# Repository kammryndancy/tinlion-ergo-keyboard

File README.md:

# tinlion-ergo-keyboard

Keyboard layout and PCB customized for my hands specifically.

Generated using https://ergogen.cache.works/

PCB edited on KiCAD - PCBEditor

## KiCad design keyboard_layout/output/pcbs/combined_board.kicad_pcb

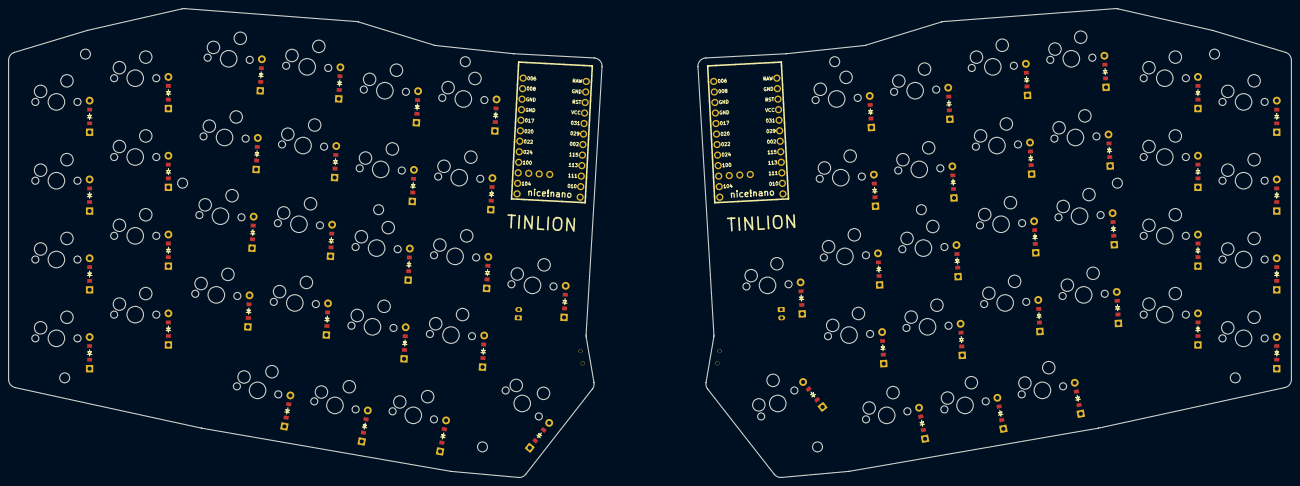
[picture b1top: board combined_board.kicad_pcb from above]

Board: 2 copper layers, 309.3 x 113.0 mm, 122 parts (0 on the bottom side), 84 nets, no tracks yet.

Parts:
D1, D2, D3, D4, D5, D6, D7, D8, D9, D10, D11, D12, D13, D14, D15, D16, D17, D18, D19, D20, D21, D22, D23, D24, D25, D26, D27, D28, D29, D30, D31, D32, D33, D34, D35, D36, D37, D38, D39, D40, D41, D42, D43, D44, D45, D46, D47, D48, D49, D50, D51, D52, D53, D54, D55, D56, D57, D58: ComboDiode
JST1, JST2: JST_PH_S2B-PH-K_02x2.00mm_Angled
MCU1, MCU2: nice_nano
S1, S2, S3, S4, S5, S6, S7, S8, S9, S10, S11, S12, S13, S14, S15, S16, S17, S18, S19, S20, S21, S22, S23, S24, S25, S26, S27, S28, S29, S30, S31, S32, S33, S34, S35, S36, S37, S38, S39, S40, S41, S42, S43, S44, S45, S46, S47, S48, S49, S50, S51, S52, S53, S54, S55, S56, S57, S58: MX
T1, T2: SPDT_C128955

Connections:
GND: JST1.2, JST2.2, MCU1.3, MCU1.4, MCU1.23, MCU2.3, MCU2.4, MCU2.23
P002: D2.1, D6.1, D10.1, D14.1, D18.1, D22.1, D29.1, D31.1, D35.1, D39.1, D43.1, D47.1, D51.1, D58.1, MCU1.18, MCU2.18
P006: MCU1.1, MCU2.1
P008: MCU1.2, MCU2.2
P009: MCU1.13, MCU2.13
P010: MCU1.14, MCU2.14
P011: MCU1.10, MCU2.10, S17.1, S18.1, S19.1, S20.1, S26.1, S46.1, S47.1, S48.1, S49.1, S55.1
P017: MCU1.5, MCU2.5, S28.1, S29.1, S57.1, S58.1
P020: MCU1.6, MCU2.6, S1.1, S2.1, S3.1, S4.1, S30.1, S31.1, S32.1, S33.1
P022: MCU1.7, MCU2.7, S5.1, S6.1, S7.1, S8.1, S34.1, S35.1, S36.1, S37.1
P024: MCU1.8, MCU2.8, S9.1, S10.1, S11.1, S12.1, S38.1, S39.1, S40.1, S41.1
P029: D3.1, D7.1, D11.1, D15.1, D19.1, D23.1, D32.1, D36.1, D40.1, D44.1, D48.1, D52.1, MCU1.19, MCU2.19
P031: D4.1, D8.1, D12.1, D16.1, D20.1, D24.1, D33.1, D37.1, D41.1, D45.1, D49.1, D53.1, MCU1.20, MCU2.20
P100: MCU1.9, MCU2.9, S13.1, S14.1, S15.1, S16.1, S25.1, S42.1, S43.1, S44.1, S45.1, S54.1
P101: MCU1.31, MCU2.31
P102: MCU1.32, MCU2.32
P104: MCU1.11, MCU2.11, S21.1, S22.1, S23.1, S24.1, S27.1, S50.1, S51.1, S52.1, S53.1, S56.1
P106: MCU1.12, MCU2.12
P107: MCU1.33, MCU2.33
P111: MCU1.15, MCU2.15
P113: D25.1, D26.1, D27.1, D28.1, D54.1, D55.1, D56.1, D57.1, MCU1.16, MCU2.16
P115: D1.1, D5.1, D9.1, D13.1, D17.1, D21.1, D30.1, D34.1, D38.1, D42.1, D46.1, D50.1, MCU1.17, MCU2.17
RAW: MCU1.24, MCU2.24, T1.2, T2.2
RST: MCU1.22, MCU2.22
VCC: MCU1.21, MCU2.21
curly_square: D29.2, S29.2
far_thumb: D27.2, S27.2
five_bottom: D21.2, S21.2
five_home: D22.2, S22.2
five_number: D24.2, S24.2
five_qwerty: D23.2, S23.2
four_bottom: D17.2, S17.2
four_home: D18.2, S18.2
four_number: D20.2, S20.2
four_qwerty: D19.2, S19.2
function_keys_bottom: D1.2, S1.2
function_keys_home: D2.2, S2.2
function_keys_number: D4.2, S4.2
function_keys_qwerty: D3.2, S3.2
home_thumb: D26.2, S26.2
mirror_curly_square: D58.2, S58.2
mirror_far_thumb: D56.2, S56.2
mirror_five_bottom: D50.2, S50.2
mirror_five_home: D51.2, S51.2
mirror_five_number: D53.2, S53.2
mirror_five_qwerty: D52.2, S52.2
mirror_four_bottom: D46.2, S46.2
mirror_four_home: D47.2, S47.2
mirror_four_number: D49.2, S49.2
mirror_four_qwerty: D48.2, S48.2
mirror_function_keys_bottom: D30.2, S30.2
mirror_function_keys_home: D31.2, S31.2
mirror_function_keys_number: D33.2, S33.2
mirror_function_keys_qwerty: D32.2, S32.2
mirror_home_thumb: D55.2, S55.2
mirror_near_thumb: D54.2, S54.2
mirror_one_bottom: D34.2, S34.2
mirror_one_home: D35.2, S35.2
mirror_one_number: D37.2, S37.2
mirror_one_qwerty: D36.2, S36.2
mirror_space_thumb: D57.2, S57.2
mirror_three_bottom: D42.2, S42.2
mirror_three_home: D43.2, S43.2
mirror_three_number: D45.2, S45.2
mirror_three_qwerty: D44.2, S44.2
mirror_two_bottom: D38.2, S38.2
mirror_two_home: D39.2, S39.2
mirror_two_number: D41.2, S41.2
mirror_two_qwerty: D40.2, S40.2
near_thumb: D25.2, S25.2
one_bottom: D5.2, S5.2
one_home: D6.2, S6.2
one_number: D8.2, S8.2
one_qwerty: D7.2, S7.2
pos: JST1.1, JST2.1, T1.1, T2.1
space_thumb: D28.2, S28.2
three_bottom: D13.2, S13.2
three_home: D14.2, S14.2
three_number: D16.2, S16.2
three_qwerty: D15.2, S15.2
two_bottom: D9.2, S9.2
two_home: D10.2, S10.2
two_number: D12.2, S12.2
two_qwerty: D11.2, S11.2

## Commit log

2024-09-08 Initial commit, base configuration
2024-09-08 Commit layout changes
2024-09-08 Update pcb size
2024-09-09 Move mount screw holes
2024-09-09 gerberfiles added, leftright pcbs
2024-09-17 Update final keyboard pcb
